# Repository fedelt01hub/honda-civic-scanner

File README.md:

# 🚗 K-Lino — Escáner K-Line y telemetría BLE (compatible con Honda Civic 96–00)

Sistema integral de diagnóstico OBD y telemetría en tiempo real para **Honda Civic 1999 (PCM P2P / Motor D16Y8)** utilizando el conector **DLC de 3 pines**, microcontrolador **ESP32-C3** con Bluetooth Low Energy (BLE 5.0) y transceptor **L9637D**.

Incluye:
1. **Firmware ESP32-C3**: Driver de bajo nivel para el protocolo K-Line patentado de Honda (9600 baud, half-duplex) y servidor BLE Nordic UART Service (NUS) a 20 Hz.
2. **Web Dashboard PWA**: Aplicación web progresiva con Web Bluetooth API, instrumentación digital/analógica estilo Type-R, shift lights, lectura de códigos DTC y logueo de datos.
3. **Documentación de hardware**: Esquema electrónico, pines DLC, transceptor y recomendaciones de ensamble.

---

## 📁 Estructura del Repositorio

| Archivo / Directorio | Descripción |
|---|---|
| [`honda-civic-scanner.ino`](honda-civic-scanner.ino) | Firmware principal ESP32-C3 (BLE NUS, ciclo de polling a la ECU y streaming binario). |
| [`honda_kline.h`](honda_kline.h) | Estructuras de telemetría (RPM, VSS, TPS, MAP, ECT, IAT, O2, marchas, etc.) y constantes. |
| [`honda_kline.cpp`](honda_kline.cpp) | Implementación del protocolo K-Line: wake-up pulse, checksums, handshake y decodificación. |
| [`dashboard_html.h`](dashboard_html.h) | Interfaz web embebida en memoria Flash (`PROGMEM`) para visualización directa. |
| [`platformio.ini`](platformio.ini) | Configuración de compilación para PlatformIO (target `esp32-c3-devkitm-1`). |
| [`flash.sh`](flash.sh) | Script bash para compilar y flashear el ESP32 por USB. |
| [`app/`](app/) | PWA independiente (HTML5/CSS3/JS) con Web Bluetooth, Service Worker y modo offline. |
| [`GUIA_CONEXION_Y_ARMADO.md`](GUIA_CONEXION_Y_ARMADO.md) | Diagrama de pines DLC 3 pines, circuito L9637D y guía de armado paso a paso. |
| [`serve_https.py`](serve_https.py) | Servidor local HTTPS para pruebas de Web Bluetooth en navegadores móviles. |
| [`csv/`](csv/) | Registros de telemetría de prueba en ruta real para análisis y calibración. |

---

## ⚡ Conexión de Hardware

El Honda Civic 1999 utiliza el conector azul de 3 pines ubicado debajo de la guantera del copiloto:
* **Pin 1 (+12V Batería)**
* **Pin 2 (GND Tierra)**
* **Pin 3 (K-Line / Comunicación bidireccional con la ECU)**

El transceptor **L9637D** convierte la señal de 12V del bus K-Line a los niveles lógicos de 3.3V requeridos por el **ESP32-C3** (GPIO 4 RX / GPIO 5 TX).

Consulta [`GUIA_CONEXION_Y_ARMADO.md`](GUIA_CONEXION_Y_ARMADO.md) para ver los diagramas detallados de los pines y resistencias de pull-up.

---

## 🚀 Compilación y Flasheo del Firmware

### Requisitos:
* [PlatformIO Core (CLI)](https://platformio.org/) o extensión de PlatformIO en VS Code.

### Pasos:
```bash
# Compilar
pio run

# Flashear al ESP32-C3 (ajustar puerto si es necesario)
./flash.sh
```

---

## 📱 Tablero Web PWA (Dashboard)

La aplicación web se conecta de forma directa al ESP32 a través de **Web Bluetooth API**:
* **Despliegue en vivo**: [https://fedelt01hub.github.io/civic-obd/](https://fedelt01hub.github.io/civic-obd/)
* Compatible con navegadores con soporte Web Bluetooth (Google Chrome / Brave en Android, Windows, Mac y Linux con flags habilitados).

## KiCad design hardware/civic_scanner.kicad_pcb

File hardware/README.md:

# PCB del escáner K-Line (Honda Civic, DLC de 3 pines)

Placa de 66 × 42 mm y 2 capas que sustituye el montaje en perfboard (ESP32-C3 + L9637D + LM2596).
Todo el diseño se genera con scripts, así que es reproducible.

| Bloque | Pieza | Notas |
|---|---|---|
| Entrada DLC | J1: 3 pads para soldar el cable adaptador Honda→OBD2 cortado | K = OBD2 p7, 12V = p16, GND = p4/5 |
| Protección | F1 PTC 500 mA 60 V, D2 SS34 (inversión), D1 SMBJ18A (TVS) | |
| 12 V → 5 V | U1 AP63205WU + L1 4,7 µH | buck síncrono de 2 A |
| USB-C | J2 HRO TYPE-C-31-M-12, U4 USBLC6-2SC6, CC 5,1 k | programación por el USB nativo (IO18/IO19) |
| OR 5 V | D3/D4 B5819W | se puede alimentar por el coche y por USB a la vez |
| 3,3 V | U2 AP2112K-3.3 (600 mA) | |
| MCU | U3 ESP32-C3-WROOM-02-N4 | la antena sobresale del borde superior, con keep-out |
| K-Line | U5 L9637D, R6 1 k 1 W pull-up | RX = IO4, TX = IO5 (igual que el firmware) |
| Interfaz | SW1 RESET, SW2 BOOT (IO9), 3 LEDs junto al USB-C: PWR (blanco, +5V), STATUS (amarillo, IO8), K-LINE (rojo, actividad del bus); TPs | |

## Regenerar

```bash
KP="/c/Program Files/KiCad/10.0/bin/python.exe"
cd hardware/scripts
"$KP" gen_sch.py        # esquemático
"$KP" gen_3d.py         # modelos 3D simplificados (USB-C y JST)
"$KP" gen_pcb.py        # colocación + rutas a mano (routes.py) + autorouter A* (autoroute.py) + zonas GND
"$KP" export_fab.py     # ERC/DRC (se detiene si hay errores) + Gerbers/taladros/BOM/CPL/PDF/renders
```

## Fabricación (JLCPCB)

En `fab/` están estos archivos:
- `civic_scanner-gerbers.zip`: va en el pedido de PCB (2 capas, 1,6 mm, HASL sin plomo o ENIG).
- `civic_scanner-bom-jlcpcb.csv` y `civic_scanner-cpl-jlcpcb.csv`: se usan para el ensamble PCBA, solo por la cara superior.
- `civic_scanner-erc.rpt` y `civic_scanner-drc.rpt`: 0 errores, 0 violaciones y 0 pads sin conectar.

Antes de pedir conviene revisar dos cosas:
- **Rotaciones del CPL:** compruébalas en la vista previa de JLCPCB, sobre todo U1/U2/U4 (SOT), U5 (SOIC-8), J2 y los LEDs. KiCad y JLC no siempre comparten el cero de rotación.
- **J1:** no va en el BOM. Son pads donde se suelda a mano el cable.
- **Disponibilidad:** confirma el stock de cada LCSC el día del pedido.

## Carcasa

La carcasa imprimible 3D (base + tapa en STL) está en `enclosure/`; ver `enclosure/README.md`.

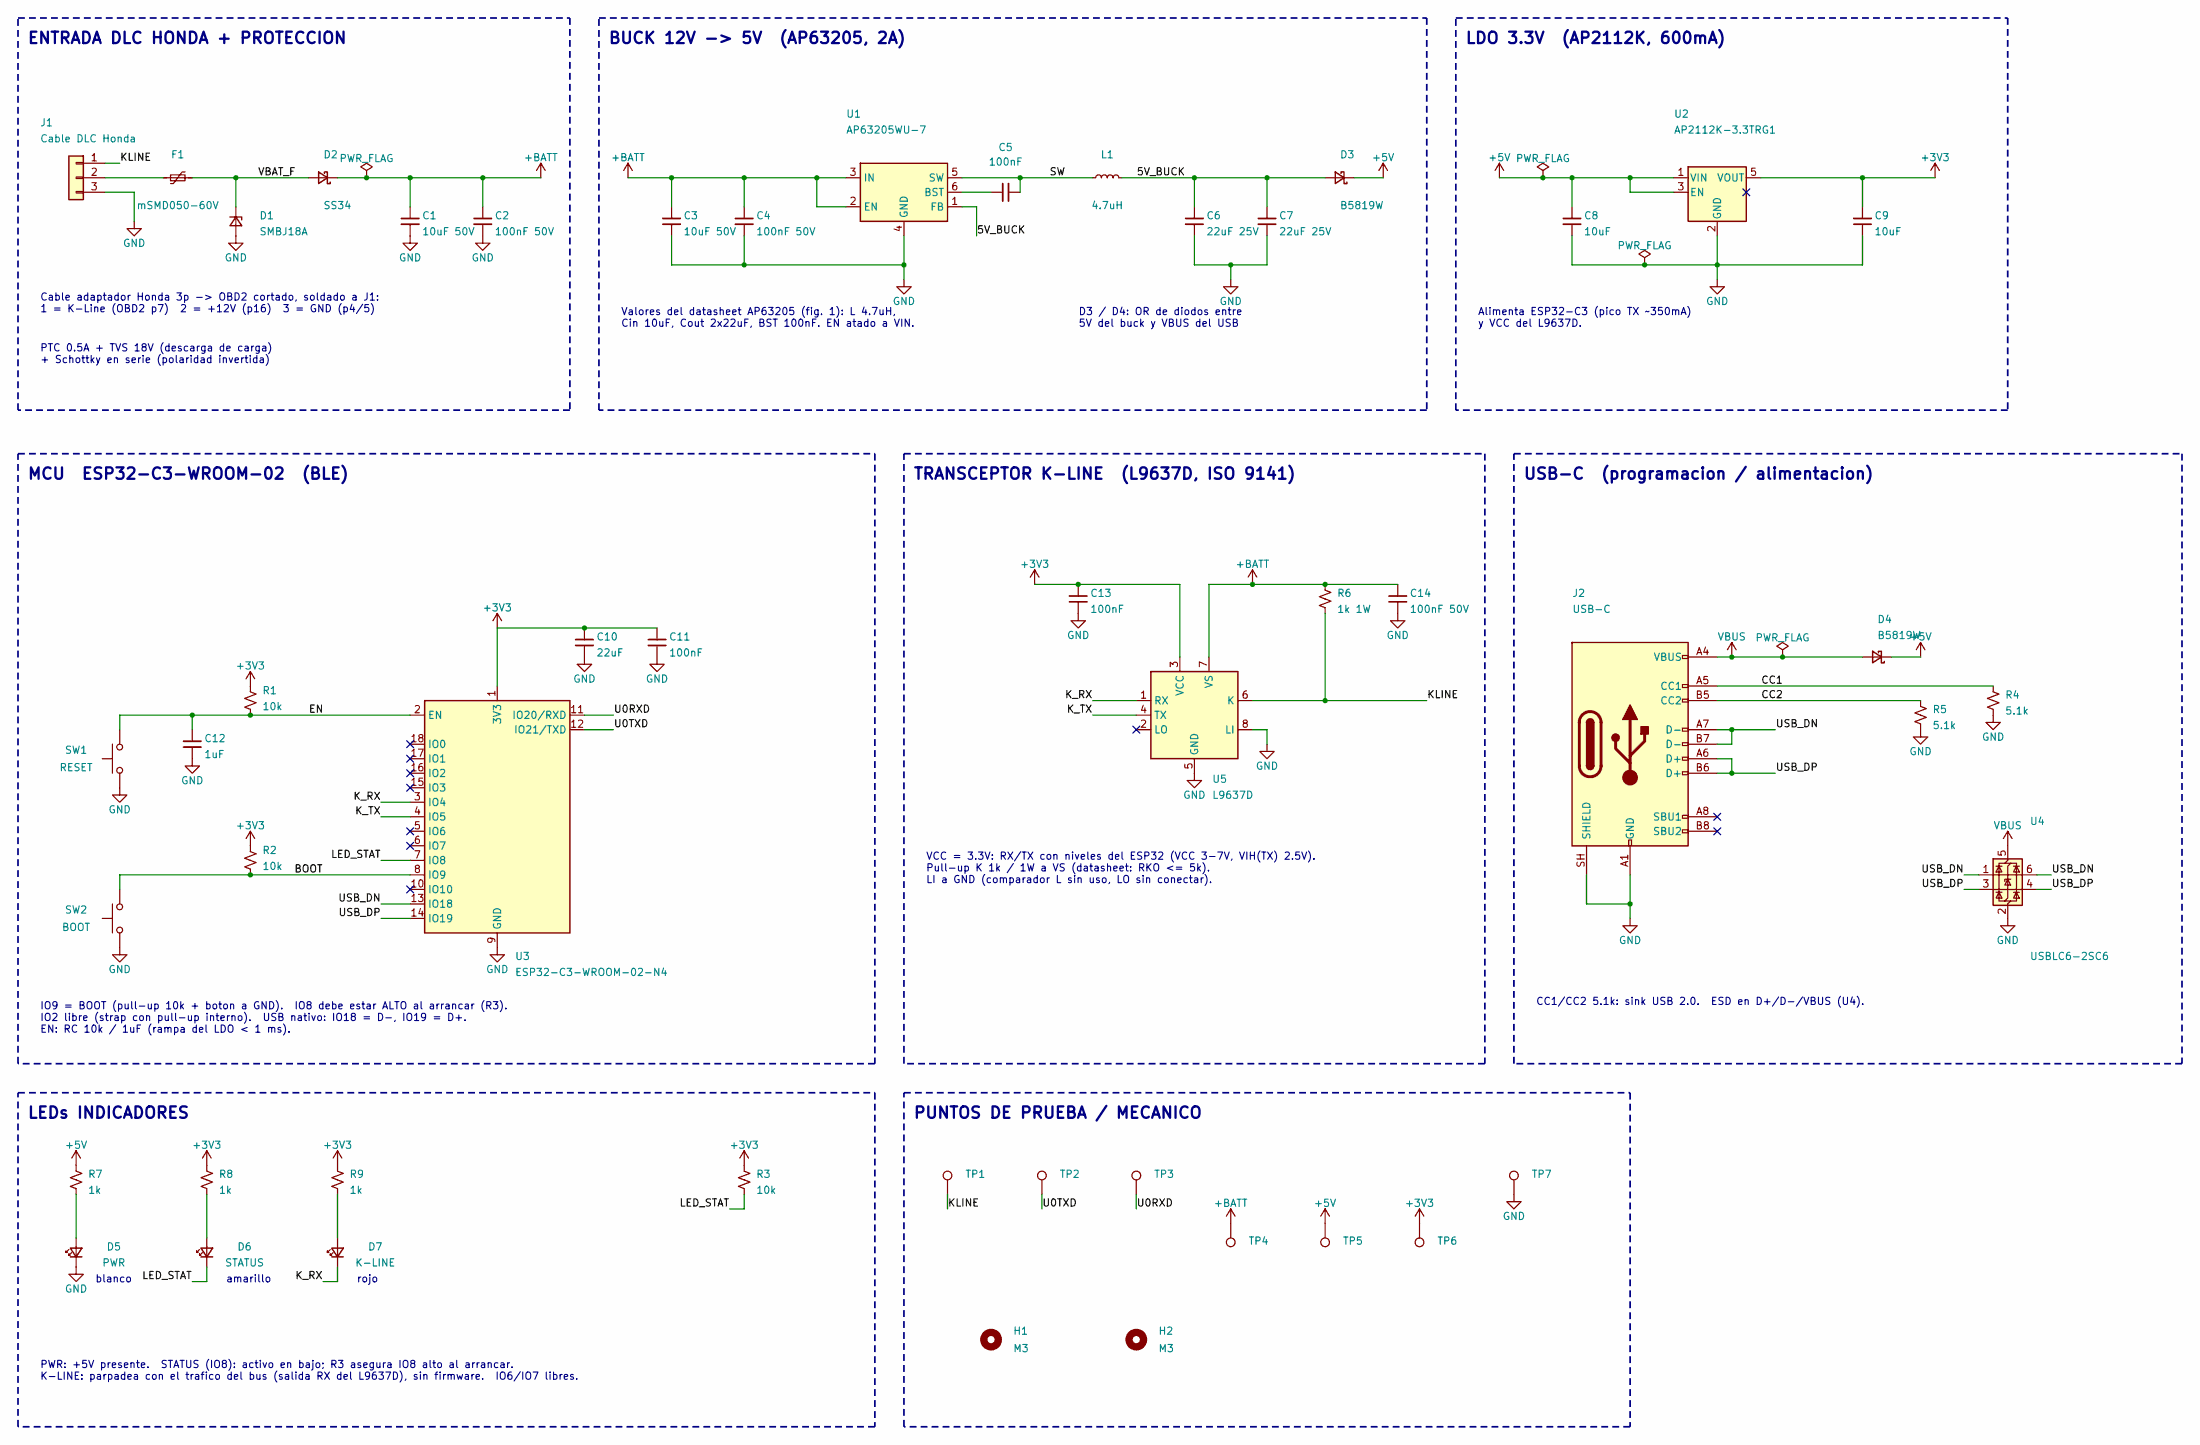
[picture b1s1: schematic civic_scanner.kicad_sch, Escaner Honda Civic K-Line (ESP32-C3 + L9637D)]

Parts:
C1, C3: 10uF 50V; C_1210_3225Metric; MPN GRM32ER71H106KA12L; LCSC C77102
C2, C4, C14: 100nF 50V; C_0603_1608Metric; MPN CC0603KRX7R9BB104; LCSC C14663
C5, C11, C13: 100nF; C_0603_1608Metric; MPN CC0603KRX7R9BB104; LCSC C14663
C6, C7: 22uF 25V; C_1206_3216Metric; MPN CL31A226KAHNNNE; LCSC C12891
C8, C9: 10uF; C_0805_2012Metric; MPN CL21A106KAYNNNE; LCSC C15850
C10: 22uF; C_0805_2012Metric; MPN CL21A226MAQNNNE; LCSC C45783
C12: 1uF; C_0603_1608Metric; MPN CL10A105KB8NNNC; LCSC C15849
D1: SMBJ18A; D_SMB; MPN SMBJ18A; LCSC C353379
D2: SS34; D_SMA; MPN SS34; LCSC C8678
D3, D4: B5819W; D_SOD-123; MPN B5819W SL; LCSC C8598
D5: PWR; LED_0603_1608Metric; MPN KT-0603W; LCSC C2290
D6: STATUS; LED_0603_1608Metric; MPN NCD0603Y2; LCSC C89811
D7: K-LINE; LED_0603_1608Metric; MPN KT-0603R; LCSC C2286
F1: mSMD050-60V; Fuse_1812_4532Metric; MPN mSMD050-60V; LCSC C70113
H1, H2: M3; MountingHole_3.2mm_M3
J1: Cable DLC Honda; Cable_Wire_1x03_P3.96mm
J2: USB-C; USB_C_Receptacle_HRO_TYPE-C-31-M-12; MPN TYPE-C-31-M-12; LCSC C165948
L1: 4.7uH; L_Changjiang_FNR4030S; MPN FNR4030S4R7MT; LCSC C167874
R1, R2, R3: 10k; R_0603_1608Metric; MPN 0603WAF1002T5E; LCSC C25804
R4, R5: 5.1k; R_0603_1608Metric; MPN 0603WAF5101T5E; LCSC C23186
R6: 1k 1W; R_2512_6332Metric; MPN 25121WF1001T4E; LCSC C54315
R7, R8, R9: 1k; R_0603_1608Metric; MPN 0603WAF1001T5E; LCSC C21190
SW1: RESET; SW_Push_1P1T_XKB_TS-1187A; MPN TS-1187A-B-A-B; LCSC C318884
SW2: BOOT; SW_Push_1P1T_XKB_TS-1187A; MPN TS-1187A-B-A-B; LCSC C318884
TP1: KLINE; TestPoint_Pad_D1.5mm
TP2: U0TXD; TestPoint_Pad_D1.5mm
TP3: U0RXD; TestPoint_Pad_D1.5mm
TP4: +BATT; TestPoint_Pad_D1.5mm
TP5: +5V; TestPoint_Pad_D1.5mm
TP6: +3V3; TestPoint_Pad_D1.5mm
TP7: GND; TestPoint_Pad_D1.5mm
U1: AP63205WU-7; TSOT-23-6; MPN AP63205WU-7; LCSC C2071056
U2: AP2112K-3.3TRG1; SOT-23-5; MPN AP2112K-3.3TRG1; LCSC C51118
U3: ESP32-C3-WROOM-02-N4; ESP32-C3-WROOM-02_JLC; MPN ESP32-C3-WROOM-02-N4; LCSC C2934560
U4: USBLC6-2SC6; SOT-23-6; MPN USBLC6-2SC6; LCSC C2687116
U5: L9637D; SOIC-8_3.9x4.9mm_P1.27mm; MPN E-L9637D013TR; LCSC C153038

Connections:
+3V3: C9.1, C10.1, C11.1, C13.1, R1.1, R2.1, R3.1, R8.1, R9.1, TP6.1, U2.5 (VOUT), U3.1 (3V3), U5.3 (VCC)
+5V: C8.1, D3.1 (K), D4.1 (K), R7.1, TP5.1, U2.1 (VIN), U2.3 (EN)
+BATT: C1.1, C2.1, C3.1, C4.1, C14.1, D2.1 (K), R6.1, TP4.1, U1.2 (EN), U1.3 (IN), U5.7 (VS)
/5V_BUCK: C6.1, C7.1, D3.2 (A), L1.2, U1.1 (FB)
/BOOT: R2.2, SW2.2, U3.8 (IO9)
/CC1: J2.A5 (CC1), R4.1
/CC2: J2.B5 (CC2), R5.1
/EN: C12.1, R1.2, SW1.2, U3.2 (EN)
/KLINE: J1.1, R6.2, TP1.1, U5.6 (K)
/K_RX: D7.1 (K), U3.3 (IO4), U5.1 (RX)
/K_TX: U3.4 (IO5), U5.4 (TX)
/LED_STAT: D6.1 (K), R3.2, U3.7 (IO8)
/SW: C5.2, L1.1, U1.5 (SW)
/U0RXD: TP3.1, U3.11 (IO20/RXD)
/U0TXD: TP2.1, U3.12 (IO21/TXD)
/USB_DN: J2.A7 (D-), J2.B7 (D-), U3.13 (IO18), U4.1 (I/O1), U4.6 (I/O1)
/USB_DP: J2.A6 (D+), J2.B6 (D+), U3.14 (IO19), U4.3 (I/O2), U4.4 (I/O2)
/VBAT_F: D1.1 (K), D2.2 (A), F1.2
GND: C1.2, C2.2, C3.2, C4.2, C6.2, C7.2, C8.2, C9.2, C10.2, C11.2, C12.2, C13.2, C14.2, D1.2 (A), D5.1 (K), J1.3, J2.A1 (GND), J2.A12 (GND), J2.B1 (GND), J2.B12 (GND), J2.SH (SHIELD), R4.2, R5.2, SW1.1, SW2.1, TP7.1, U1.4 (GND), U2.2 (GND), U3.9 (GND), U3.19 (GND), U4.2 (GND), U5.5 (GND), U5.8 (LI)
unnamed: D5.2 (A), R7.2
unnamed: D6.2 (A), R8.2
unnamed: D7.2 (A), R9.2
unnamed: F1.1, J1.2
unnamed: C5.1, U1.6 (BST)
VBUS: D4.2 (A), J2.A4 (VBUS), J2.A9 (VBUS), J2.B4 (VBUS), J2.B9 (VBUS), U4.5 (VBUS)

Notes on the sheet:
ENTRADA DLC HONDA + PROTECCION
Cable adaptador Honda 3p -> OBD2 cortado, soldado a J1: 1 = K-Line (OBD2 p7) 2 = +12V (p16) 3 = GND (p4/5)
PTC 0.5A + TVS 18V (descarga de carga) + Schottky en serie (polaridad invertida)
BUCK 12V -> 5V (AP63205, 2A)
Valores del datasheet AP63205 (fig. 1): L 4.7uH, Cin 10uF, Cout 2x22uF, BST 100nF. EN atado a VIN.
D3 / D4: OR de diodos entre 5V del buck y VBUS del USB
LDO 3.3V (AP2112K, 600mA)
Alimenta ESP32-C3 (pico TX ~350mA) y VCC del L9637D.
USB-C (programacion / alimentacion)
CC1/CC2 5.1k: sink USB 2.0. ESD en D+/D-/VBUS (U4).
MCU ESP32-C3-WROOM-02 (BLE)
IO9 = BOOT (pull-up 10k + boton a GND). IO8 debe estar ALTO al arrancar (R3). IO2 libre (strap con pull-up interno). USB nativo: IO18 = D-, IO19 = D+. EN: RC 10k / 1uF (rampa del LDO < 1 ms).
TRANSCEPTOR K-LINE (L9637D, ISO 9141)
VCC = 3.3V: RX/TX con niveles del ESP32 (VCC 3-7V, VIH(TX) 2.5V). Pull-up K 1k / 1W a VS (datasheet: RKO <= 5k). LI a GND (comparador L sin uso, LO sin conectar).
LEDs INDICADORES
blanco
amarillo
rojo
PWR: +5V presente. STATUS (IO8): activo en bajo; R3 asegura IO8 alto al arrancar. K-LINE: parpadea con el trafico del bus (salida RX del L9637D), sin firmware. IO6/IO7 libres.
PUNTOS DE PRUEBA / MECANICO

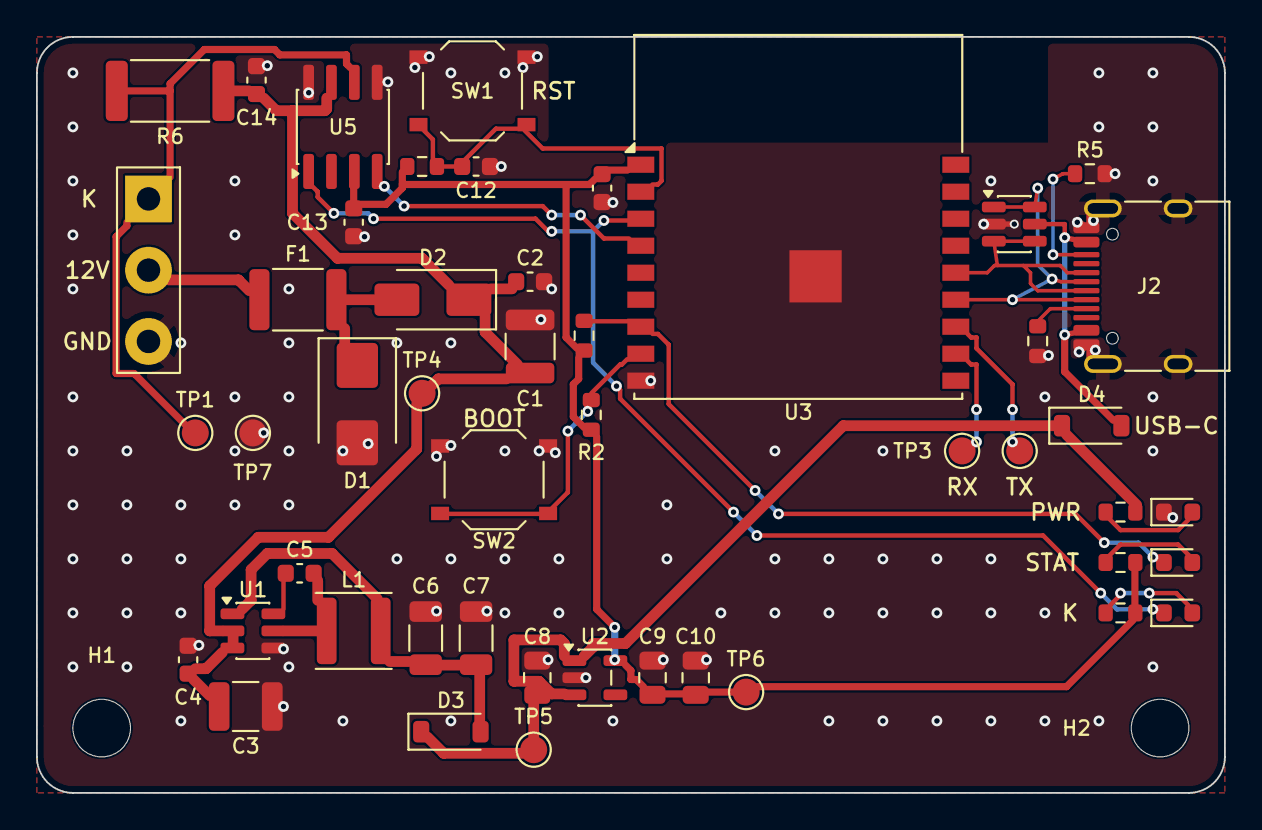
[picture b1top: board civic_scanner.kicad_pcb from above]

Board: 2 copper layers, 66.0 x 42.0 mm, 50 parts (0 on the bottom side), 25 nets.

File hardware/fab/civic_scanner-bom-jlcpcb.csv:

Comment,Designator,Footprint,LCSC,Qty,MPN,Manufacturer
10uF 50V,"C1,C3",C_1210_3225Metric,C77102,2,GRM32ER71H106KA12L,Murata
100nF 50V,"C2,C4,C14",C_0603_1608Metric,C14663,3,CC0603KRX7R9BB104,YAGEO
100nF,"C5,C11,C13",C_0603_1608Metric,C14663,3,CC0603KRX7R9BB104,YAGEO
22uF 25V,"C6,C7",C_1206_3216Metric,C12891,2,CL31A226KAHNNNE,Samsung
10uF,"C8,C9",C_0805_2012Metric,C15850,2,CL21A106KAYNNNE,Samsung
22uF,C10,C_0805_2012Metric,C45783,1,CL21A226MAQNNNE,Samsung
1uF,C12,C_0603_1608Metric,C15849,1,CL10A105KB8NNNC,Samsung
SMBJ18A,D1,D_SMB,C353379,1,SMBJ18A,Jingdao
SS34,D2,D_SMA,C8678,1,SS34,MDD
B5819W,"D3,D4",D_SOD-123,C8598,2,B5819W SL,Changjiang
PWR,D5,LED_0603_1608Metric,C2290,1,KT-0603W,Hubei KENTO
STATUS,D6,LED_0603_1608Metric,C89811,1,NCD0603Y2,NATIONSTAR
K-LINE,D7,LED_0603_1608Metric,C2286,1,KT-0603R,Hubei KENTO
mSMD050-60V,F1,Fuse_1812_4532Metric,C70113,1,mSMD050-60V,Shenzhen JDT
USB-C,J2,USB_C_Receptacle_HRO_TYPE-C-31-M-12,C165948,1,TYPE-C-31-M-12,Korean Hroparts
4.7uH,L1,L_Changjiang_FNR4030S,C167874,1,FNR4030S4R7MT,Changjiang
10k,R1-R3,R_0603_1608Metric,C25804,3,0603WAF1002T5E,UNI-ROYAL
5.1k,"R4,R5",R_0603_1608Metric,C23186,2,0603WAF5101T5E,UNI-ROYAL
1k 1W,R6,R_2512_6332Metric,C54315,1,25121WF1001T4E,UNI-ROYAL
1k,R7-R9,R_0603_1608Metric,C21190,3,0603WAF1001T5E,UNI-ROYAL
RESET,SW1,SW_Push_1P1T_XKB_TS-1187A,C318884,1,TS-1187A-B-A-B,XKB Connection
BOOT,SW2,SW_Push_1P1T_XKB_TS-1187A,C318884,1,TS-1187A-B-A-B,XKB Connection
AP63205WU-7,U1,TSOT-23-6,C2071056,1,AP63205WU-7,Diodes Inc
AP2112K-3.3TRG1,U2,SOT-23-5,C51118,1,AP2112K-3.3TRG1,Diodes Inc
ESP32-C3-WROOM-02-N4,U3,ESP32-C3-WROOM-02_JLC,C2934560,1,ESP32-C3-WROOM-02-N4,Espressif
USBLC6-2SC6,U4,SOT-23-6,C2687116,1,USBLC6-2SC6,UMW
L9637D,U5,SOIC-8_3.9x4.9mm_P1.27mm,C153038,1,E-L9637D013TR,STMicroelectronics

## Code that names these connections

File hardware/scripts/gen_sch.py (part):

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                fields=F("civic_scanner:Cable_Wire_1x03_P3.96mm", None, None, None,
                         "1=K-Line 2=+12V 3=GND (Honda DLC)"),
                ref_at=(4.5, 10.2), val_at=(4.5, 11.3))
    s.pin_label(J1, "1", "KLINE", stub=1)
    F1 = s.part("F1", "Device:Polyfuse_Small", "mSMD050-60V", (14, 14), rot=90,
                fields=F("Fuse:Fuse_1812_4532Metric", "C70113", "mSMD050-60V", "Shenzhen JDT", "PTC 0.5A hold 60V"),
                ref_at=(14, 12.4), val_at=(14, 15.9))
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                fields=F("Diode_SMD:D_SMA", "C8678", "SS34", "MDD", "Reverse polarity 40V 3A"),
                ref_at=(24, 12.4), val_at=(24, 15.9))
    s.wire(F1.p("2"), D2.p("2"), net="VBAT_F")
    s.label("VBAT_F", U(19.5, 14), (1, 0))
    s.wire(U(18, 14), D1.p("1"), net="VBAT_F")
    s.junction(U(18, 14))
    s.pin_power(D1, "2", "GND")
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    s.wire(J2.p("A7"), U(121, 52), U(121, 53), J2.p("B7"), net="USB_DN")
    s.wire(U(121, 52), U(124, 52), net="USB_DN")
    s.junction(U(121, 52))
    s.label("USB_DN", U(124, 52), (1, 0))
    s.wire(J2.p("A6"), U(121, 54), U(121, 55), J2.p("B6"), net="USB_DP")
    s.wire(U(121, 55), U(124, 55), net="USB_DP")
    s.junction(U(121, 55))
    s.label("USB_DP", U(124, 55), (1, 0))
    s.pin_nc(J2, "A8")
    s.pin_nc(J2, "B8")
    s.wire(J2.p("SH"), U(111, 64), U(114, 64))
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                fields=F("Package_TO_SOT_SMD:SOT-23-6", "C2687116", "USBLC6-2SC6", "UMW"),
                ref_at=(141.5, 58.3), val_at=(141.5, 67.6))
    # I/O1 = D-, I/O2 = D+ (pin swap for a clean layout; the TVS lines are symmetric)
    s.pin_label(U4, "1", "USB_DN")
    s.pin_label(U4, "3", "USB_DP")
    s.pin_label(U4, "6", "USB_DN")
    s.pin_label(U4, "4", "USB_DP")
    s.pin_power(U4, "5", "VBUS")
    s.pin_power(U4, "2", "GND")
    s.text("CC1/CC2 5.1k: sink USB 2.0.  ESD en D+/D-/VBUS (U4).", (107.5, 70.5), size=1.27, bold=False)
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        s.pin_label(U3, pn, net, stub=2)
    for pn in ("18", "17", "16", "15", "10", "5", "6"):
        s.pin_nc(U3, pn)
    s.pin_label(U3, "11", "U0RXD", stub=2)
    s.pin_label(U3, "12", "U0TXD", stub=2)
    s.pin_power(U3, "9", "GND")
    x33, y33 = U3.p("1")
    s.wire((x33, y33), (x33, mm(45)), U(47, 45))
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    U5 = s.part("U5", "civic_scanner:L9637D", "L9637D", (84, 51),
                fields=F("Package_SO:SOIC-8_3.9x4.9mm_P1.27mm", "C153038", "E-L9637D013TR", "STMicroelectronics"),
                ref_at=(85.2, 55.4), val_at=(85.2, 56.5))
    s.pin_label(U5, "1", "K_RX", stub=3)
    s.pin_label(U5, "4", "K_TX", stub=3)
    s.pin_nc(U5, "2")
    s.pin_power(U5, "5", "GND")
    xv, yv = U5.p("3")
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    s.wire((xk, yk), (mm(100), yk), net="KLINE")
    s.wire(R6.p("2"), (mm(93), yk), net="KLINE")
    s.junction((mm(93), yk))
    s.label("KLINE", (mm(100), yk), (1, 0))
    s.pin_power(U5, "8", "GND", stub=1)
    s.text("VCC = 3.3V: RX/TX con niveles del ESP32 (VCC 3-7V, VIH(TX) 2.5V).\nPull-up K 1k / 1W a VS (datasheet: RKO <= 5k).\nLI a GND (comparador L sin uso, LO sin conectar).",
           (65.5, 60.5), size=1.27, bold=False)
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    s.pin_power(R3, "1", "+3V3")
    r3x, r3y = R3.p("2")
    s.wire((r3x, r3y), (r3x, r3y + G), (r3x - G, r3y + G), net="LED_STAT")
    s.label("LED_STAT", (r3x - G, r3y + G), (-1, 0))
    s.text("PWR: +5V presente.  STATUS (IO8): activo en bajo; R3 asegura IO8 alto al arrancar.\nK-LINE: parpadea con el trafico del bus (salida RX del L9637D), sin firmware.  IO6/IO7 libres.",
           (4.5, 95.5), size=1.27, bold=False)

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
